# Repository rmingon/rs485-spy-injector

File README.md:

# ESP32 RS485 Hacker Suite

### _Sniff, Inject, and Control RS485 Communication from Your Phone_

## Overview

**ESP32 RS485 Hacker Suite** is a mobile-integrated toolkit built around the ESP32 microcontroller, designed to interact with RS485-based communication systems. This system allows for full control, inspection, and injection of RS485 traffic — making it a valuable asset for penetration testers, reverse engineers, and industrial system analysts.

## Features

- **RS485 Sniffing**  
  Monitor and log communication over RS485 in raw hex format. Useful for debugging, protocol analysis, or reverse engineering.

- **Hex Injection (Manual & Presets)**  
  Send custom hex data manually or use predefined presets. This supports use cases like device emulation, protocol fuzzing, or triggering specific system behaviors.

- **Mobile App Interface**  
  Control every feature directly from a smartphone via a dedicated app. Includes interfaces for configuration, command sending, and history review.

- **Dual RS485 Bus Support**  
  Work with two independent RS485 buses, ideal for simultaneously observing and injecting data into separate lines.

- **WiFi Configuration**  
  Easily connect your ESP32 to a local network or operate it in AP mode.

- **Command Presets**  
  Create and store frequently used hex commands for rapid execution.

- **Reception History**  
  View a log of all received data, enabling traffic inspection and replay.

## Ethical Hacking Applications

> **Important:** This tool is provided for **authorized use only**. Unauthorized access or tampering with industrial systems is illegal and unethical.

- Reverse engineering RS485-based protocols (MODBUS RTU, proprietary systems, etc.)
- Pen-testing building automation hardware (e.g., HVAC, elevator controllers, door access systems)
- Replay attacks or fault injection to test system resilience
- Simulating RS485 slave/master devices
- Forensic logging of unsecured RS485 data transmissions

## Hardware

- ESP32 (WROOM or S3 variant recommended)
- Dual RS485 transceivers (e.g., MAX485)
- Level shifters and protection diodes
- Power supply (USB or external)
- Custom PCB (designed in KiCad)

## Mobile App Overview

- Configure each RS485 bus individually
- Set baud rates and communication parameters
- Enter and send custom hex data manually
- Create named command presets (e.g., open door)
- View reception history for each bus

## Quick Example

```
Preset: Open door
Command: 09 21 32 AA B2
Target Device: Access Controller
Result: Relay Triggered, Door Unlocked
```

## Getting Started

### Flashing Firmware

1. Upload `main.cpp` to your ESP32 using Arduino IDE or PlatformIO.
2. Power on the device and connect via serial or mobile app.
3. Configure your RS485 settings and network preferences.

### Using the App

1. Connect to the ESP32 over WiFi.
2. Select Bus 1 or Bus 2.
3. Set the appropriate baud rate.
4. Send hex data manually or use a saved preset.
5. Monitor the reception log for data.

## Protocols Supported

- MODBUS RTU
- BACnet MS/TP (partial)
- Custom/Proprietary RS485 protocols
- Most serial-based building and industrial control protocols

## Disclaimer

This tool is meant for **educational, testing, and research** purposes only. Use it exclusively on systems you own or have explicit permission to test.

**You are fully responsible for how this tool is used. Unauthorized access or tampering with live systems can lead to legal consequences.**

5. **Use and Modify** the project under CERN-OHL v2 license.

## License

This project is licensed under the **CERN Open Hardware Licence Version 2**. See `LICENSE` file for full terms.

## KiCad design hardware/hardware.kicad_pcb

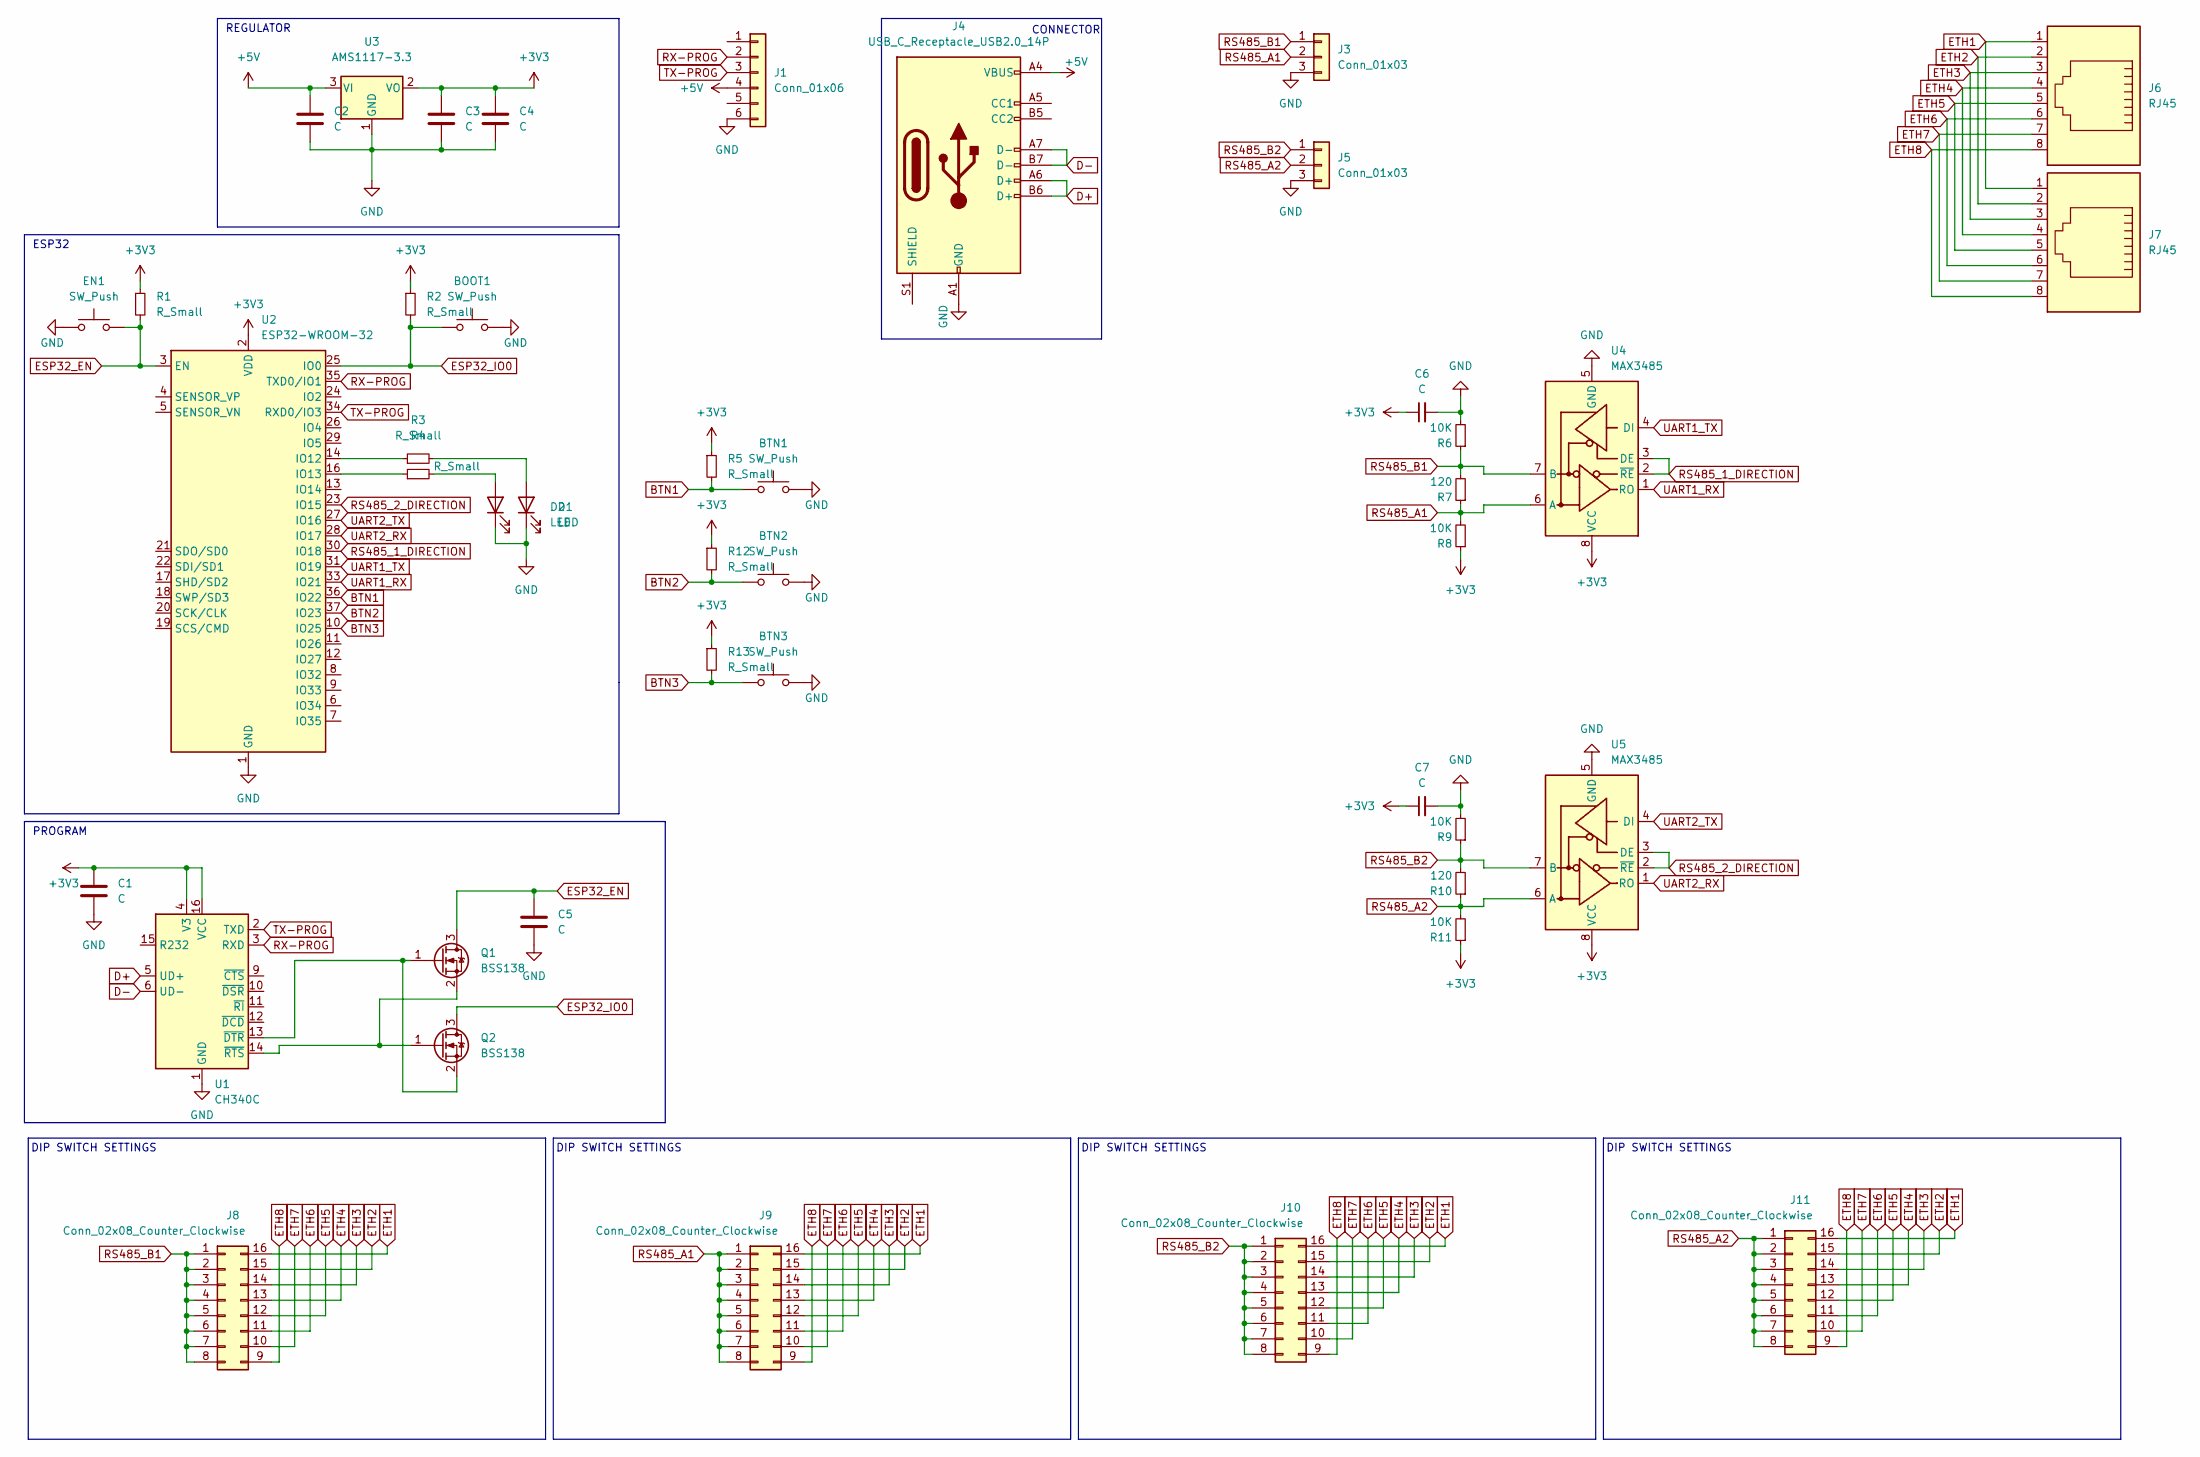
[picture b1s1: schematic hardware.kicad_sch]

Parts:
BOOT1: SW_Push; SW_SPST_FSMSM; LCSC C398053
BTN1, BTN2, BTN3: SW_Push; SW_SPST_FSMSM; LCSC C398053
C1, C2, C4: C; C_0603_1608Metric; LCSC C30926
C3, C5: C; C_0603_1608Metric; LCSC C19702
C6, C7: C; C_0603_1608Metric; LCSC C106245
D1: LED; LED_0603_1608Metric; LCSC C19171301
D2: LED; LED_0603_1608Metric; LCSC C434425
EN1: SW_Push; SW_SPST_FSMSM; LCSC C398053
J1: Conn_01x06; PinHeader_1x06_P2.54mm_Vertical
J3, J5: Conn_01x03; TerminalBlock_4Ucon_1x03_P3.50mm_Horizontal
J4: USB_C_Receptacle_USB2.0_14P; USB_C_Receptacle_JAE_DX07S016JA1R1500; LCSC C963213
J6, J7: RJ45; RJ45_Amphenol_RJHSE5380
J8, J9, J10, J11: Conn_02x08_Counter_Clockwise; SW_DIP_SPSTx08_Slide_6.7x21.88mm_W8.61mm_P2.54mm_LowProfile; LCSC C3293158
Q1, Q2: BSS138; SOT-23; LCSC C7420338
R1, R2, R5, R12, R13: R_Small; R_0603_1608Metric; LCSC C98220
R3, R4: R_Small; R_0603_1608Metric; LCSC C2906975
R6, R8, R9, R11: 10K; R_0603_1608Metric; LCSC C22975
R7, R10: 120; R_0603_1608Metric; LCSC C22975
U1: CH340C; SOIC-16_3.9x9.9mm_P1.27mm; LCSC C84681
U2: ESP32-WROOM-32; LCSC C82899
U3: AMS1117-3.3; SOT-223-3_TabPin2; LCSC C6186
U4, U5: MAX3485; SOIC-8_3.9x4.9mm_P1.27mm; LCSC C9943

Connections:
+3V3: C1.1, C3.1, C4.1, C6.1, C7.1, R1.1, R2.1, R5.1, R8.1, R11.1, R12.1, R13.1, U1.4 (V3), U1.16 (VCC), U2.2 (VDD), U3.2 (VO), U4.8 (VCC), U5.8 (VCC)
+5V: C2.1, J1.4, J4.A4 (VBUS), J4.A9 (VBUS), J4.B4 (VBUS), J4.B9 (VBUS), U3.3 (VI)
BTN1: BTN1.1, R5.2, U2.36 (IO22)
BTN2: BTN2.1, R12.2, U2.37 (IO23)
BTN3: BTN3.1, R13.2, U2.10 (IO25)
D+: J4.A6 (D+), J4.B6 (D+), U1.5 (UD+)
D-: J4.A7 (D-), J4.B7 (D-), U1.6 (UD-)
ESP32_EN: C5.1, EN1.2, Q1.3 (D), R1.2, U2.3 (EN)
ESP32_IO0: BOOT1.1, Q2.3 (D), R2.2, U2.25 (IO0)
ETH1: J6.1, J7.1, J8.16, J9.16, J10.16, J11.16
ETH2: J6.2, J7.2, J8.15, J9.15, J10.15, J11.15
ETH3: J6.3, J7.3, J8.14, J9.14, J10.14, J11.14
ETH4: J6.4, J7.4, J8.13, J9.13, J10.13, J11.13
ETH5: J6.5, J7.5, J8.12, J9.12, J10.12, J11.12
ETH6: J6.6, J7.6, J8.11, J9.11, J10.11, J11.11
ETH7: J6.7, J7.7, J8.10, J9.10, J10.10, J11.10
ETH8: J6.8, J7.8, J8.9, J9.9, J10.9, J11.9
GND: BOOT1.2, BTN1.2, BTN2.2, BTN3.2, C1.2, C2.2, C3.2, C4.2, C5.2, C6.2, C7.2, D1.1 (K), D2.1 (K), EN1.1, J1.6, J3.3, J4.A1 (GND), J4.A12 (GND), J4.B1 (GND), J4.B12 (GND), J5.3, R6.2, R9.2, U1.1 (GND), U2.1 (GND), U2.15 (GND), U2.38 (GND), U2.39 (GND), U3.1 (GND), U4.5 (GND), U5.5 (GND)
unnamed: D1.2 (A), R4.2
unnamed: D2.2 (A), R3.2
unnamed: Q1.1 (G), Q2.2 (S), U1.13 (~DTR)
unnamed: Q1.2 (S), Q2.1 (G), U1.14 (~RTS)
unnamed: R3.1, U2.14 (IO12)
unnamed: R4.1, U2.16 (IO13)
RS485_1_DIRECTION: U2.30 (IO18), U4.2 (~RE), U4.3 (DE)
RS485_2_DIRECTION: U2.23 (IO15), U5.2 (~RE), U5.3 (DE)
RS485_A1: J3.2, J9.1, J9.2, J9.3, J9.4, J9.5, J9.6, J9.7, J9.8, R7.1, R8.2, U4.6 (A)
RS485_A2: J5.2, J11.1, J11.2, J11.3, J11.4, J11.5, J11.6, J11.7, J11.8, R10.1, R11.2, U5.6 (A)
RS485_B1: J3.1, J8.1, J8.2, J8.3, J8.4, J8.5, J8.6, J8.7, J8.8, R6.1, R7.2, U4.7 (B)
RS485_B2: J5.1, J10.1, J10.2, J10.3, J10.4, J10.5, J10.6, J10.7, J10.8, R9.1, R10.2, U5.7 (B)
RX-PROG: J1.2, U1.3 (RXD), U2.35 (TXD0/IO1)
TX-PROG: J1.3, U1.2 (TXD), U2.34 (RXD0/IO3)
UART1_RX: U2.33 (IO21), U4.1 (RO)
UART1_TX: U2.31 (IO19), U4.4 (DI)
UART2_RX: U2.28 (IO17), U5.1 (RO)
UART2_TX: U2.27 (IO16), U5.4 (DI)

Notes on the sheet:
ESP32
CONNECTOR
DIP SWITCH SETTINGS
PROGRAM
REGULATOR

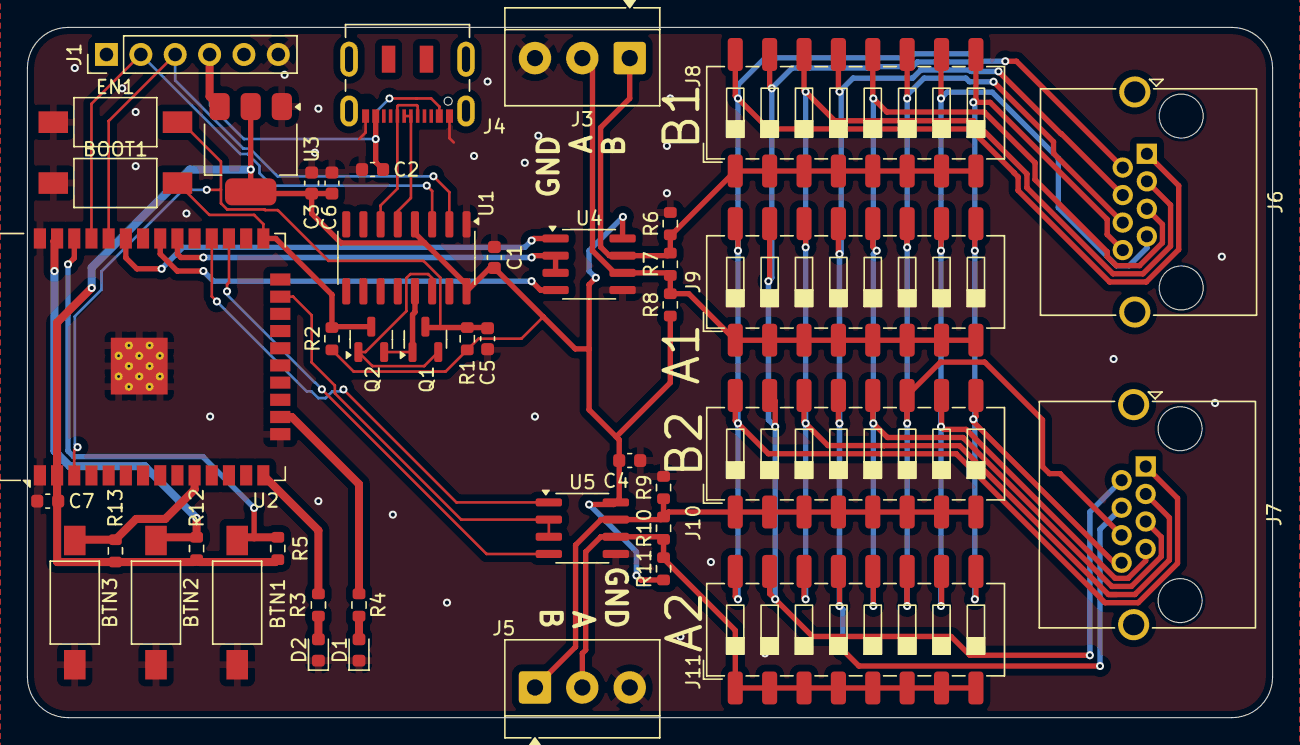
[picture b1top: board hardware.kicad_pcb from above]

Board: 2 copper layers, 92.0 x 51.0 mm, 44 parts (0 on the bottom side), 36 nets.

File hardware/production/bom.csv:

Designator,Footprint,Quantity,Value,LCSC Part #
"BOOT1, BTN1, BTN2, BTN3, EN1",SW_SPST_FSMSM,5,SW_Push,C398053
"C1, C2, C4",0603,3,C,C30926
"C3, C5",0603,2,C,C19702
"C6, C7",0603,2,C,C106245
D1,0603,1,LED,C19171301
D2,0603,1,LED,C434425
J1,PinHeader_1x06_P2.54mm_Vertical,1,Conn_01x06,
"J10, J11, J8, J9",SW_DIP_SPSTx08_Slide_6.7x21.88mm_W8.61mm_P2.54mm_LowProfile,4,Conn_02x08_Counter_Clockwise,C3293158
"J3, J5",TerminalBlock_4Ucon_1x03_P3.50mm_Horizontal,2,Conn_01x03,
J4,USB_C_Receptacle_JAE_DX07S016JA1R1500,1,USB_C_Receptacle_USB2.0_14P,C963213
"J6, J7",RJ45_Amphenol_RJHSE5380,2,RJ45,
"Q1, Q2",SOT-23,2,BSS138,C7420338
"R1, R12, R13, R2, R5",0603,5,R_Small,C98220
"R10, R7",0603,2,120,C22975
"R11, R6, R8, R9",0603,4,10K,C22975
"R3, R4",0603,2,R_Small,C2906975
U1,SOIC-16_3.9x9.9mm_P1.27mm,1,CH340C,C84681
U2,ESP32-WROOM-32,1,ESP32-WROOM-32,C82899
U3,SOT-223-3_TabPin2,1,AMS1117-3.3,C6186
"U4, U5",SOIC-8_3.9x4.9mm_P1.27mm,2,MAX3485,C9943

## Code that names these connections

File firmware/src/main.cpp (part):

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#include <WiFi.h>
#include <vector>

static constexpr int UART1_RX = 21;
static constexpr int UART1_TX = 19;
static constexpr int UART2_RX = 17;
static constexpr int UART2_TX = 16;
static constexpr int RS485_DIR1 = 18;
static constexpr int RS485_DIR2 = 15;

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
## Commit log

2025-07-19 add minimal schematic
2025-07-19 add pcb wiring
2025-07-20 rotation of ethernet connector
2025-07-20 add readme
2025-08-02 first commit firmware
2025-08-02 BT + wifi server
2025-08-02 first commit mobile app
2025-08-02 add gluestack
2025-08-02 add bus pages
2025-08-03 add mobile app file
2025-08-03 add readme + pictures
2025-08-03 remove unused files
2025-08-03 add picture in readme
